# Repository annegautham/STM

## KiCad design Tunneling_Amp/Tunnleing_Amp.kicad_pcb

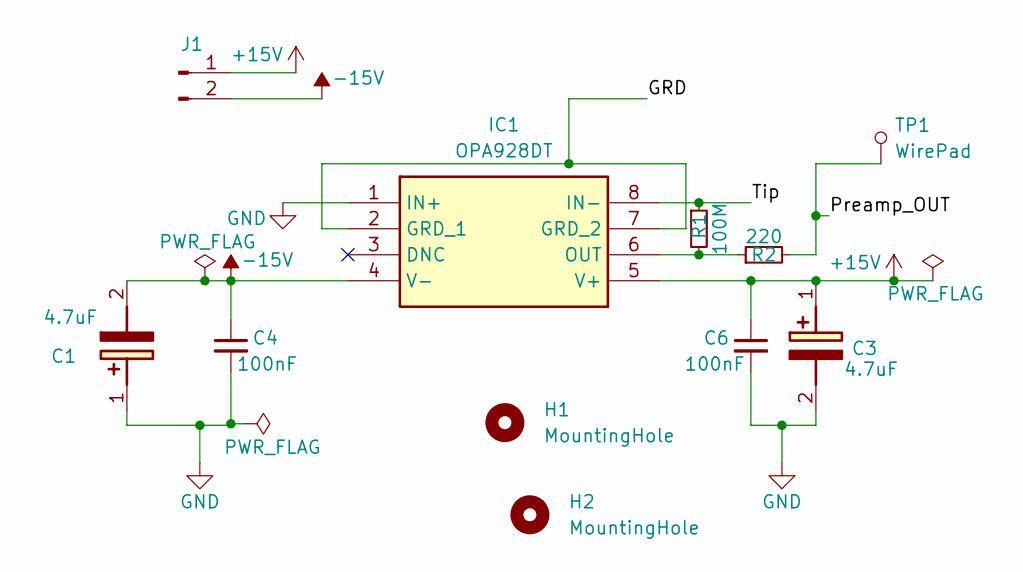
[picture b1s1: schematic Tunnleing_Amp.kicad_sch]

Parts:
C1, C3: 4.7uF; CAPPM6032X280N; Mouser Part Number 74-293D475X9035C2TE3
C4, C6: 100nF; C_0402_1005Metric; LCSC C1545
H1, H2: MountingHole; MountingHole_2.2mm_M2
IC1: OPA928DT; SOIC127P600X175-8N; Mouser Part Number 595-OPA928DT
J1: Conn_01x02_Pin; PinHeader_1x02_P2.54mm_Vertical
R1: 100M; R_0603_1608Metric; Mouser Part Number 708-HMC0603FT100M; LCSC C22962
R2: 220; R_0603_1608Metric; LCSC C22962
TP1: WirePad; PinHeader_1x01_P1.00mm_Vertical

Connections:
+15V: C3.1 (+), C6.1, IC1.5 (V+), J1.1
-15V: C1.2 (-), C4.1, IC1.4 (V-), J1.2
/GRD: IC1.2 (GRD_1), IC1.7 (GRD_2)
/Preamp_OUT: R2.2, TP1.1
/Tip: IC1.8 (IN-), R1.1
GND: C1.1 (+), C3.2 (-), C4.2, C6.2, IC1.1 (IN+)
unnamed: IC1.6 (OUT), R1.2, R2.1

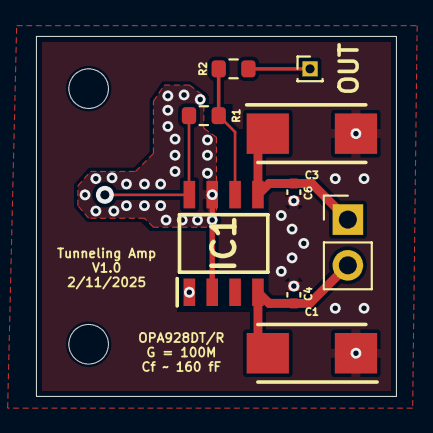
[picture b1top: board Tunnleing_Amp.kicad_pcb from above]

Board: 4 copper layers, 20.0 x 20.0 mm, 11 parts (0 on the bottom side), 7 nets.

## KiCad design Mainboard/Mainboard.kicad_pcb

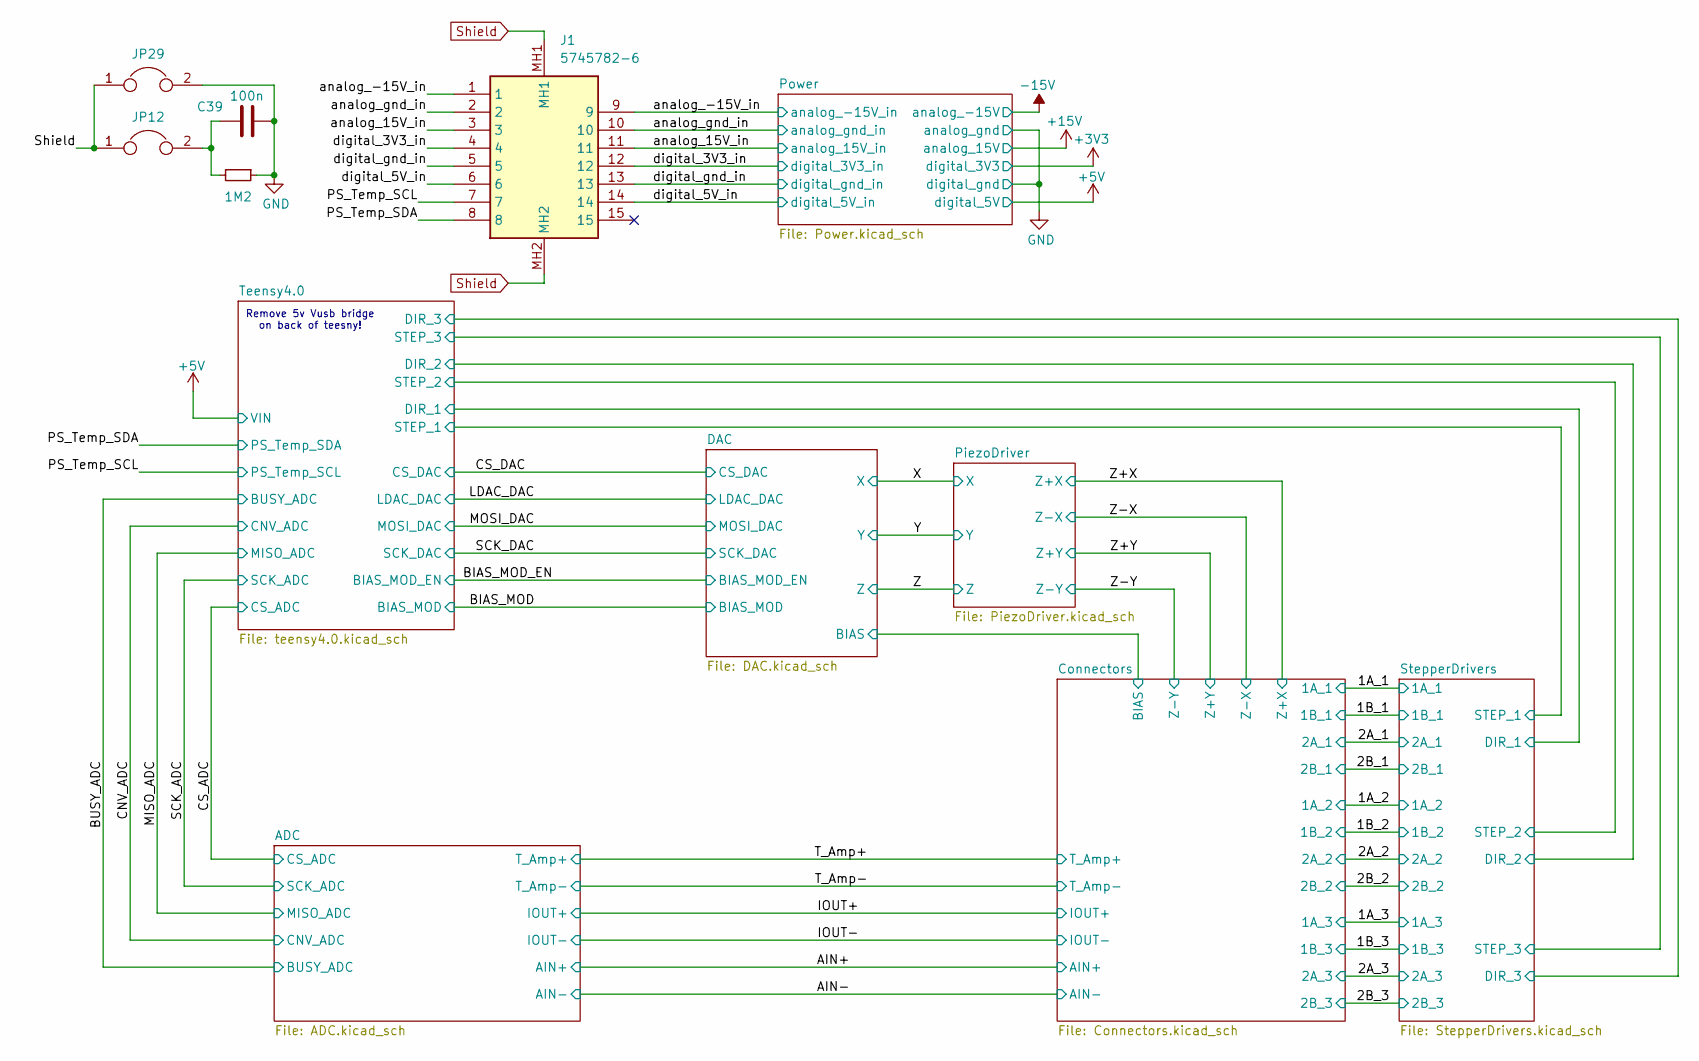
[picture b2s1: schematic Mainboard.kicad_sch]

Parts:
C39: 100n; C_0805_2012Metric; Mouser Part Number 80-C0805S104K1RACAUT; LCSC C14663
J1: 5745782-6; 57457826; Mouser Part Number 571-5745782-6
JP12, JP29: Jumper; SolderJumper-2_P1.3mm_Open_TrianglePad1.0x1.5mm
R30: 1M2; R_0805_2012Metric; Mouser Part Number 755-SDR10EZPF1204; LCSC C22107

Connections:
/PS_Temp_SCL: J1.7; also elsewhere on the board
/PS_Temp_SDA: J1.8; also elsewhere on the board
unnamed: C39.1, JP12.2, R30.2
Shield: J1.MH1, J1.MH2, JP12.1, JP29.1; also elsewhere on the board

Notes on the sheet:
Remove 5v Vusb bridge on back of teesny!

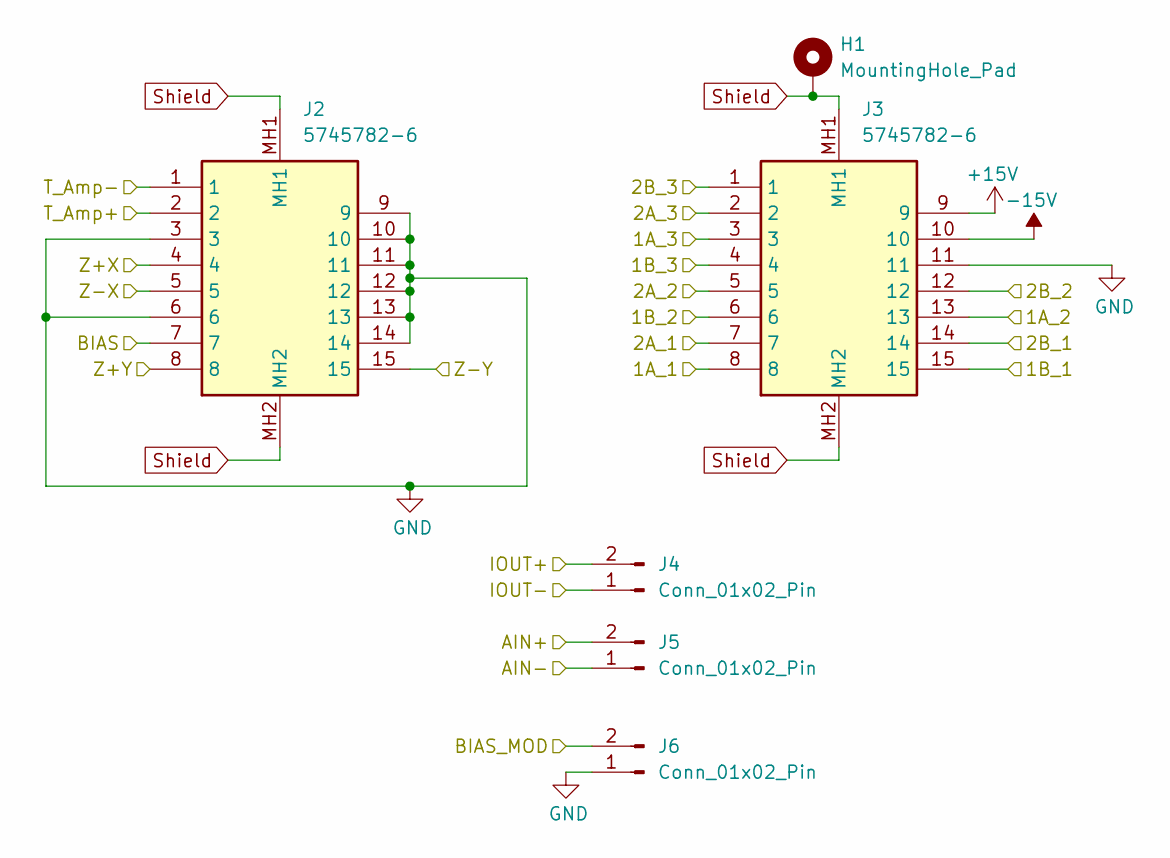
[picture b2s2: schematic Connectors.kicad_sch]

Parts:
H1: MountingHole_Pad; MountingHole_2.2mm_M2_Pad_Via
J2, J3: 5745782-6; 57457826; Mouser Part Number 571-5745782-6
J4, J5, J6: Conn_01x02_Pin; PinHeader_1x02_P2.54mm_Vertical

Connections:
/1A_1: J3.8; also elsewhere on the board
/1A_2: J3.13; also elsewhere on the board
/1A_3: J3.3; also elsewhere on the board
/1B_1: J3.15; also elsewhere on the board
/1B_2: J3.6; also elsewhere on the board
/1B_3: J3.4; also elsewhere on the board
/2A_1: J3.7; also elsewhere on the board
/2A_2: J3.5; also elsewhere on the board
/2A_3: J3.2; also elsewhere on the board
/2B_1: J3.14; also elsewhere on the board
/2B_2: J3.12; also elsewhere on the board
/2B_3: J3.1; also elsewhere on the board
/AIN+: J5.2; also elsewhere on the board
/AIN-: J5.1; also elsewhere on the board
/BIAS_MOD: J6.2; also elsewhere on the board
/Connectors/BIAS: J2.7; also elsewhere on the board
/IOUT+: J4.2; also elsewhere on the board
/IOUT-: J4.1; also elsewhere on the board
/T_Amp+: J2.2; also elsewhere on the board
/T_Amp-: J2.1; also elsewhere on the board
/Z+X: J2.4; also elsewhere on the board
/Z+Y: J2.8; also elsewhere on the board
/Z-X: J2.5; also elsewhere on the board
/Z-Y: J2.15; also elsewhere on the board
Shield: H1.1, J2.MH1, J2.MH2, J3.MH1, J3.MH2; also elsewhere on the board

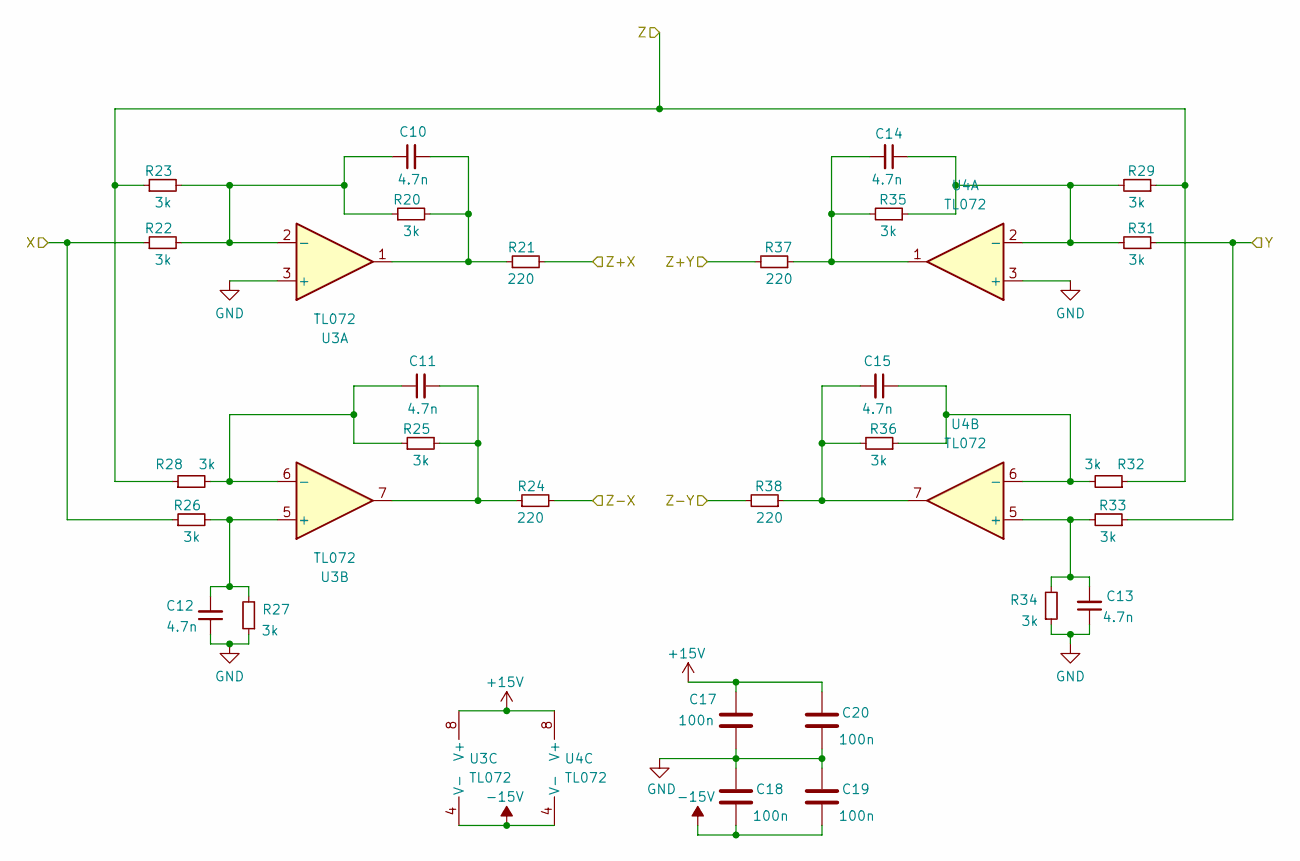
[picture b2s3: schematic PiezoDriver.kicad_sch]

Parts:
C10, C11, C12, C13, C14, C15: 4.7n; C_0805_2012Metric; Mouser Part Number 80-C0805C472J3GAUTO
C17, C18, C19, C20: 100n; C_0805_2012Metric; Mouser Part Number 80-C0805S104K1RACAUT; LCSC C14663
R20, R22, R23, R25, R26, R27, R28, R29, R31, R32, R33, R34, R35, R36: 3k; R_0805_2012Metric; Mouser Part Number 667-ERA-6AED302V
R21, R24, R37, R38: 220; R_0805_2012Metric; Mouser Part Number 279-CRGH0805F220R
U3, U4: TL072; SOIC-8-1EP_3.9x4.9mm_P1.27mm_EP2.29x3mm_ThermalVias; Mouser Part Number 511-TL072BIDT

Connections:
/X: R22.1, R26.1; also elsewhere on the board
/Y: R31.1, R33.1; also elsewhere on the board
/Z: R23.1, R28.1, R29.1, R32.1; also elsewhere on the board
/Z+X: R21.2; also elsewhere on the board
/Z+Y: R37.2; also elsewhere on the board
/Z-X: R24.2; also elsewhere on the board
/Z-Y: R38.2; also elsewhere on the board
unnamed: C10.2, R20.2, R21.1, U3.1
unnamed: C11.2, R24.1, R25.2, U3.7
unnamed: C14.2, R35.2, R37.1, U4.1
unnamed: C15.2, R36.2, R38.1, U4.7
unnamed: C10.1, R20.1, R22.2, R23.2, U3.2 (-)
unnamed: C12.2, R26.2, R27.2, U3.5 (+)
unnamed: C11.1, R25.1, R28.2, U3.6 (-)
unnamed: C14.1, R29.2, R31.2, R35.1, U4.2 (-)
unnamed: C13.2, R33.2, R34.2, U4.5 (+)
unnamed: C15.1, R32.2, R36.1, U4.6 (-)

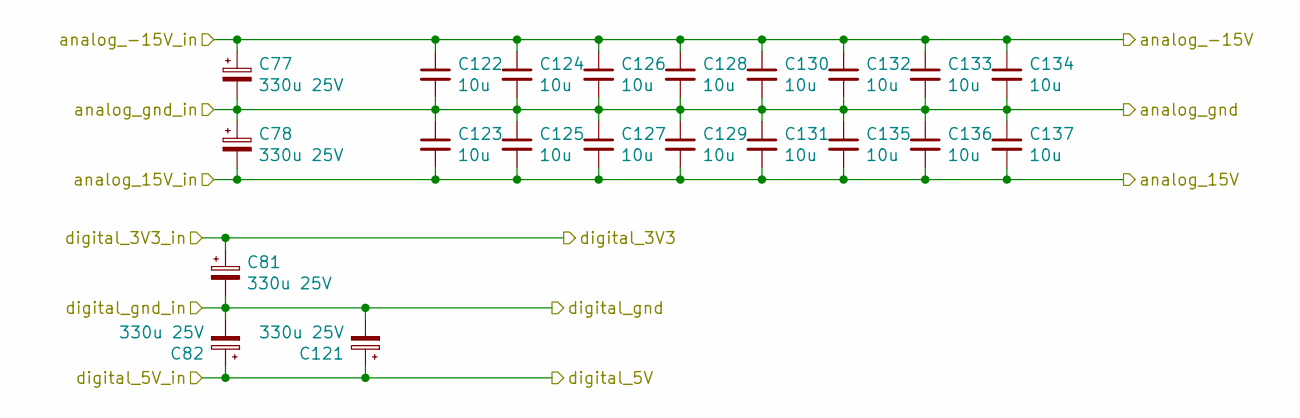
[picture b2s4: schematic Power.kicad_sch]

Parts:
C77, C78, C81, C82, C121: 330u 25V; CP_Radial_D8.0mm_P3.50mm
C122, C123, C124, C125, C126, C127, C128, C129, C130, C131, C132, C133, C134, C135, C136, C137: 10u; C_1206_3216Metric

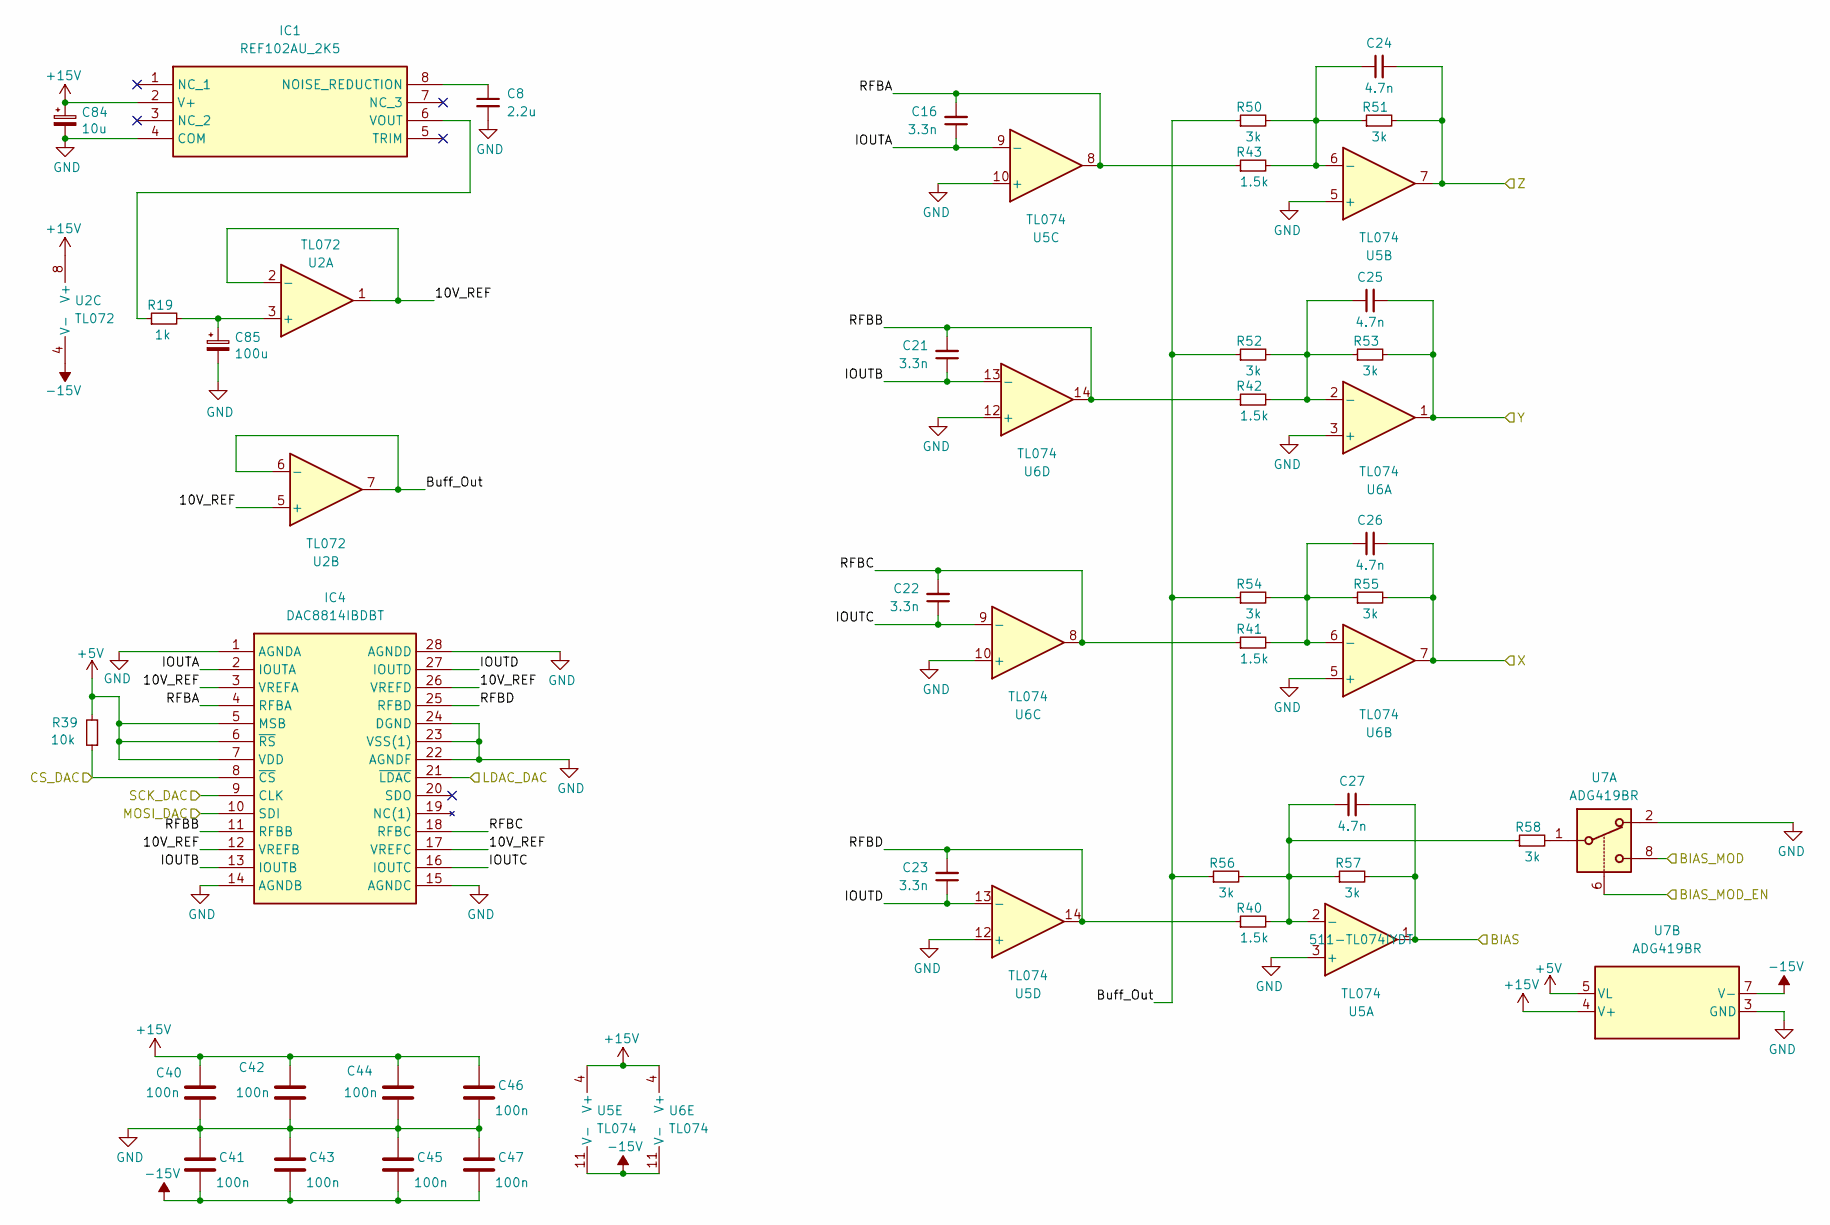
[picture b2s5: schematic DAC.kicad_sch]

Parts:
C8: 2.2u; C_0805_2012Metric; Mouser Part Number 80-C0805C225K4R3123
C16, C21, C22, C23: 3.3n; C_0805_2012Metric; Mouser Part Number 80-C0805C332KCR
C24, C25, C26, C27: 4.7n; C_0805_2012Metric; Mouser Part Number 80-C0805C472J3GAUTO
C40, C41, C42, C43, C44, C45, C46, C47: 100n; C_0805_2012Metric; Mouser Part Number 80-C0805S104K1RACAUT; LCSC C14663
C84: 10u; CP_Radial_D5.0mm_P2.00mm; Mouser Part Number 710-860020472003
C85: 100u; CP_Radial_D6.3mm_P2.50mm; Mouser Part Number 80-ESW107M016AE3EA
IC1: REF102AU_2K5; SOIC127P600X175-8N; Mouser Part Number 595-REF102AU/2K5
IC4: DAC8814IBDBT; SOP65P780X200-28N; Mouser Part Number 595-DAC8814IBDBT
R19: 1k; R_0805_2012Metric; Mouser Part Number 755-ESR10EZPJ102
R39: 10k; R_0805_2012Metric; Mouser Part Number 755-ESR10EZPD1002
R40, R41, R42, R43: 1.5k; R_0805_2012Metric; Mouser Part Number 755-ESR10EZPF1501
R50, R51, R52, R53, R54, R55, R56, R57, R58: 3k; R_0805_2012Metric; Mouser Part Number 667-ERA-6AED302V
U2: TL072; SOIC-8-1EP_3.9x4.9mm_P1.27mm_EP2.29x3mm_ThermalVias; Mouser Part Number 511-TL072BIDT
U5, U6: TL074; SOIC-14_3.9x8.7mm_P1.27mm; Mouser Part Number 511-TL074IYDT
U7: ADG419BR; SOIC-8_3.9x4.9mm_P1.27mm; Mouser Part Number 584-ADG419BRZ-R

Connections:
/BIAS_MOD: U7.8; also elsewhere on the board
/BIAS_MOD_EN: U7.6; also elsewhere on the board
/CS_DAC: IC4.8 (~CS), R39.1; also elsewhere on the board
/Connectors/BIAS: C27.2, R57.2, U5.1; also elsewhere on the board
/DAC/10V_REF: IC4.3 (VREFA), IC4.12 (VREFB), IC4.17 (VREFC), IC4.26 (VREFD), U2.1, U2.2 (-), U2.5 (+)
/DAC/Buff_Out: R50.1, R52.1, R54.1, R56.1, U2.6 (-), U2.7
/DAC/IOUTA: C16.1, IC4.2 (IOUTA), U5.9 (-)
/DAC/IOUTB: C21.1, IC4.13 (IOUTB), U6.13 (-)
/DAC/IOUTC: C22.1, IC4.16 (IOUTC), U6.9 (-)
/DAC/IOUTD: C23.1, IC4.27 (IOUTD), U5.13 (-)
/DAC/RFBA: C16.2, IC4.4 (RFBA), R43.1, U5.8
/DAC/RFBB: C21.2, IC4.11 (RFBB), R42.1, U6.14
/DAC/RFBC: C22.2, IC4.18 (RFBC), R41.1, U6.8
/DAC/RFBD: C23.2, IC4.25 (RFBD), R40.1, U5.14
/LDAC_DAC: IC4.21 (~LDAC); also elsewhere on the board
/MOSI_DAC: IC4.10 (SDI); also elsewhere on the board
/SCK_ADC: IC4.9 (CLK); also elsewhere on the board
/X: C26.2, R55.2, U6.7; also elsewhere on the board
/Y: C25.2, R53.2, U6.1; also elsewhere on the board
/Z: C24.2, R51.2, U5.7; also elsewhere on the board
unnamed: C8.1, IC1.8 (NOISE_REDUCTION)
unnamed: IC1.6 (VOUT), R19.1
unnamed: R58.2, U7.1
unnamed: C85.1, R19.2, U2.3 (+)
unnamed: C27.1, R40.2, R56.2, R57.1, R58.1, U5.2 (-)
unnamed: C24.1, R43.2, R50.2, R51.1, U5.6 (-)
unnamed: C25.1, R42.2, R52.2, R53.1, U6.2 (-)
unnamed: C26.1, R41.2, R54.2, R55.1, U6.6 (-)

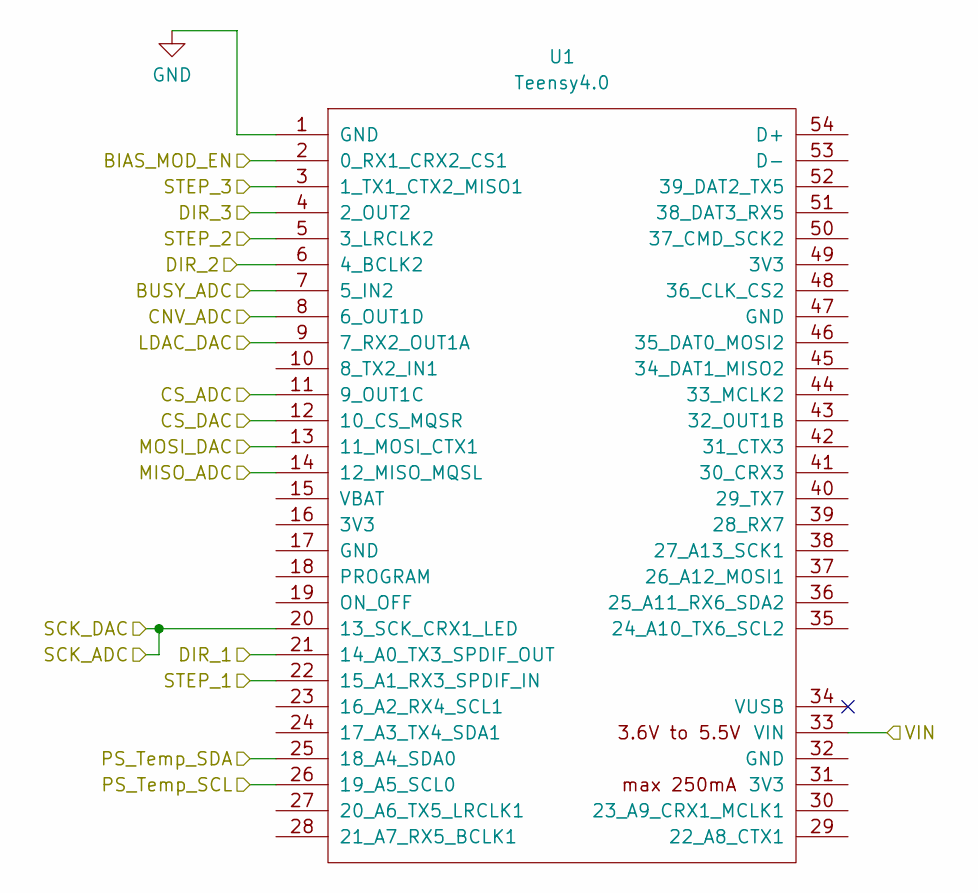
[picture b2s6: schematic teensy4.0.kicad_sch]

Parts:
U1: Teensy4.0; Teensy40

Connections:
/BIAS_MOD_EN: U1.2 (0_RX1_CRX2_CS1); also elsewhere on the board
/BUSY_ADC: U1.7 (5_IN2); also elsewhere on the board
/CNV_ADC: U1.8 (6_OUT1D); also elsewhere on the board
/CS_ADC: U1.11 (9_OUT1C); also elsewhere on the board
/CS_DAC: U1.12 (10_CS_MQSR); also elsewhere on the board
/LDAC_DAC: U1.9 (7_RX2_OUT1A); also elsewhere on the board
/MISO_ADC: U1.14 (12_MISO_MQSL); also elsewhere on the board
/MOSI_DAC: U1.13 (11_MOSI_CTX1); also elsewhere on the board
/PS_Temp_SCL: U1.26 (19_A5_SCL0); also elsewhere on the board
/PS_Temp_SDA: U1.25 (18_A4_SDA0); also elsewhere on the board
/SCK_ADC: U1.20 (13_SCK_CRX1_LED); also elsewhere on the board
/StepperDrivers/DIR_1: U1.21 (14_A0_TX3_SPDIF_OUT); also elsewhere on the board
/StepperDrivers/DIR_2: U1.6 (4_BCLK2); also elsewhere on the board
/StepperDrivers/DIR_3: U1.4 (2_OUT2); also elsewhere on the board
/StepperDrivers/STEP_1: U1.22 (15_A1_RX3_SPDIF_IN); also elsewhere on the board
/StepperDrivers/STEP_2: U1.5 (3_LRCLK2); also elsewhere on the board
/StepperDrivers/STEP_3: U1.3 (1_TX1_CTX2_MISO1); also elsewhere on the board

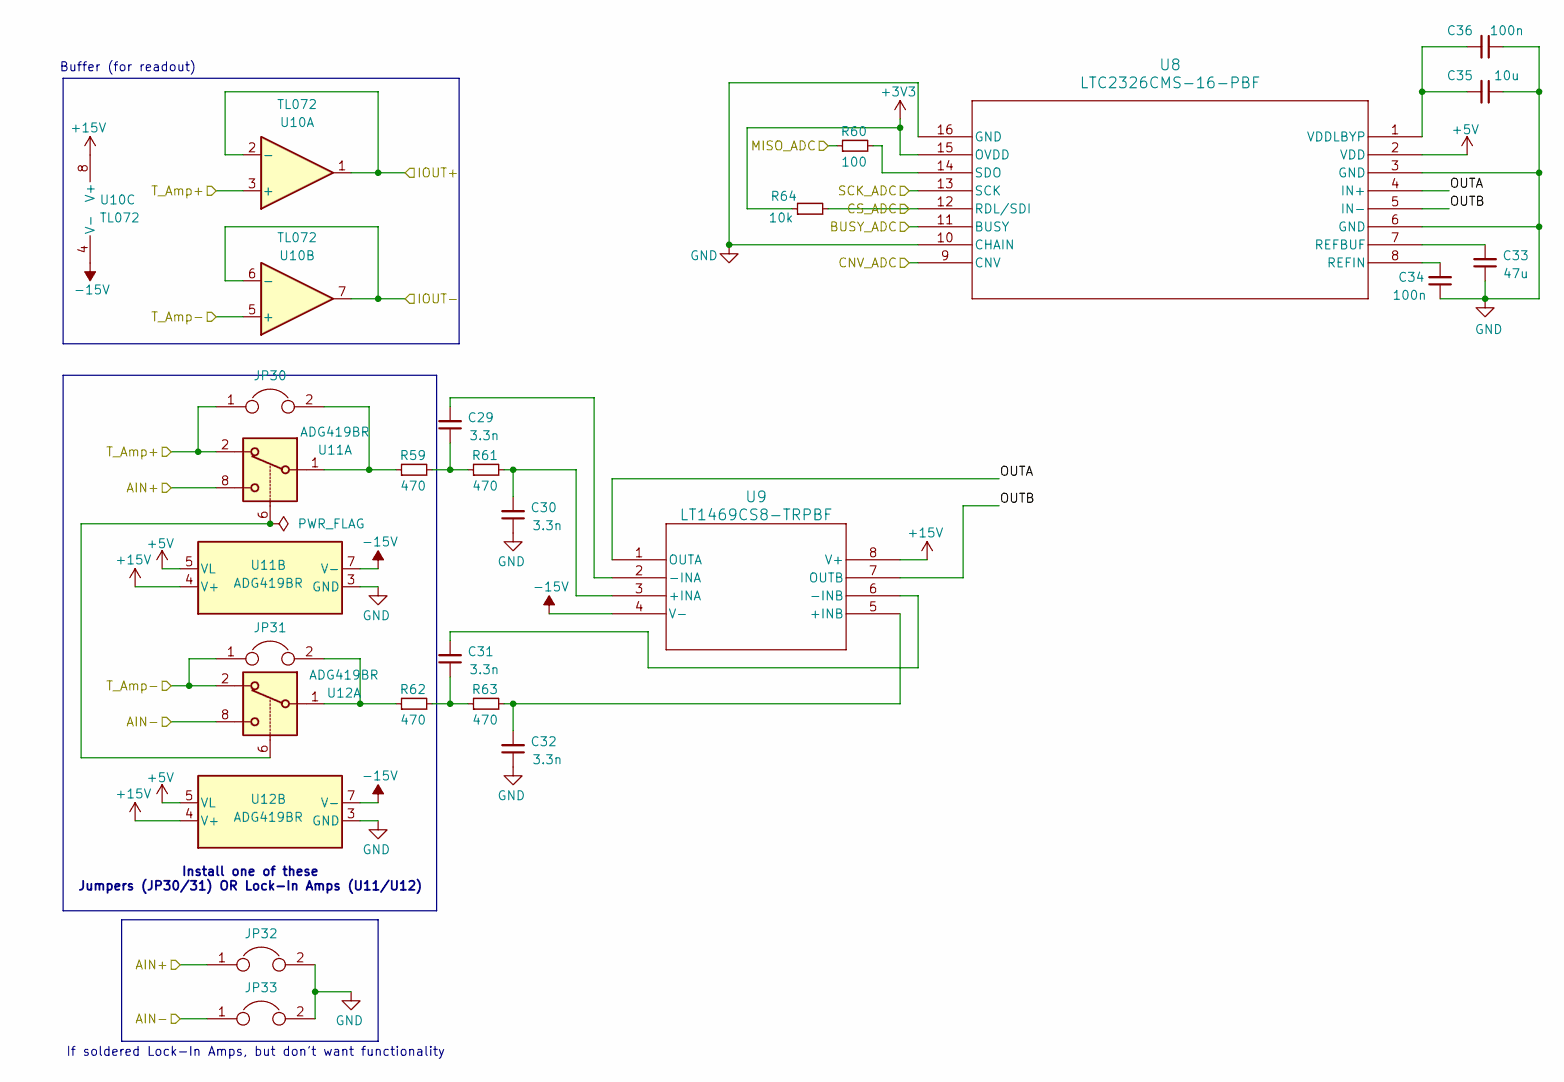
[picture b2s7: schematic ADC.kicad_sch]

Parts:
C29, C30, C31, C32: 3.3n; C_0805_2012Metric; Mouser Part Number 80-C0805C332KCR
C33: 47u; C_0805_2012Metric; Mouser Part Number 80-C0805C476M9P7800
C34, C36: 100n; C_0805_2012Metric; Mouser Part Number 80-C0805S104K1RACAUT
C35: 10u; CP_Radial_D5.0mm_P2.00mm; Mouser Part Number 710-860020472003
JP30, JP31, JP32, JP33: Jumper; SolderJumper-2_P1.3mm_Open_TrianglePad1.0x1.5mm
R59, R61, R62, R63: 470; R_0805_2012Metric; Mouser Part Number 667-ERA-6AEB471V
R60: 100; R_0805_2012Metric; Mouser Part Number 708-RNCA0805BTE100R
R64: 10k; R_0805_2012Metric; Mouser Part Number 755-ESR10EZPD1002
U8: LTC2326CMS-16-PBF; MSOP-16_MS_LIT; Mouser Part Number 584-LTC2326CMS-16PBF
U9: LT1469CS8-TRPBF; SO-8_S_LIT; Mouser Part Number 584-LT1469CS8#TRPBF
U10: TL072; SOIC-8-1EP_3.9x4.9mm_P1.27mm_EP2.29x3mm_ThermalVias; Mouser Part Number 511-TL072BIDT
U11, U12: ADG419BR; SOIC-8_3.9x4.9mm_P1.27mm; Mouser Part Number 584-ADG419BRZ-R

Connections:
/ADC/OUTA: U8.4 (IN+), U9.1 (OUTA)
/ADC/OUTB: U8.5 (IN-), U9.7 (OUTB)
/AIN+: JP32.1, U11.8; also elsewhere on the board
/AIN-: JP33.1, U12.8; also elsewhere on the board
/BUSY_ADC: U8.11 (BUSY); also elsewhere on the board
/CNV_ADC: U8.9 (CNV); also elsewhere on the board
/CS_ADC: R64.2, U8.12 (RDL/SDI); also elsewhere on the board
/IOUT+: U10.1, U10.2 (-); also elsewhere on the board
/IOUT-: U10.6 (-), U10.7; also elsewhere on the board
/MISO_ADC: R60.1; also elsewhere on the board
/SCK_ADC: U8.13 (SCK); also elsewhere on the board
/T_Amp+: JP30.1, U10.3 (+), U11.2; also elsewhere on the board
/T_Amp-: JP31.1, U10.5 (+), U12.2; also elsewhere on the board
unnamed: C29.1, R59.2, R61.1
unnamed: C31.1, R62.2, R63.1
unnamed: JP30.2, R59.1, U11.1
unnamed: JP31.2, R62.1, U12.1
unnamed: C33.2, U8.7 (REFBUF)
unnamed: C34.2, U8.8 (REFIN)
unnamed: R60.2, U8.14 (SDO)
unnamed: C35.2, C36.2, U8.1 (VDDLBYP)
unnamed: C30.2, R61.2, U9.3 (+INA)
unnamed: C32.2, R63.2, U9.5 (+INB)
unnamed: C29.2, U9.2 (-INA)
unnamed: C31.2, U9.6 (-INB)
unnamed: U11.6, U12.6

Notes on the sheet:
Install one of these Jumpers (JP30/31) OR Lock-In Amps (U11/U12)
If soldered Lock-In Amps, but don't want functionality
Buffer (for readout)

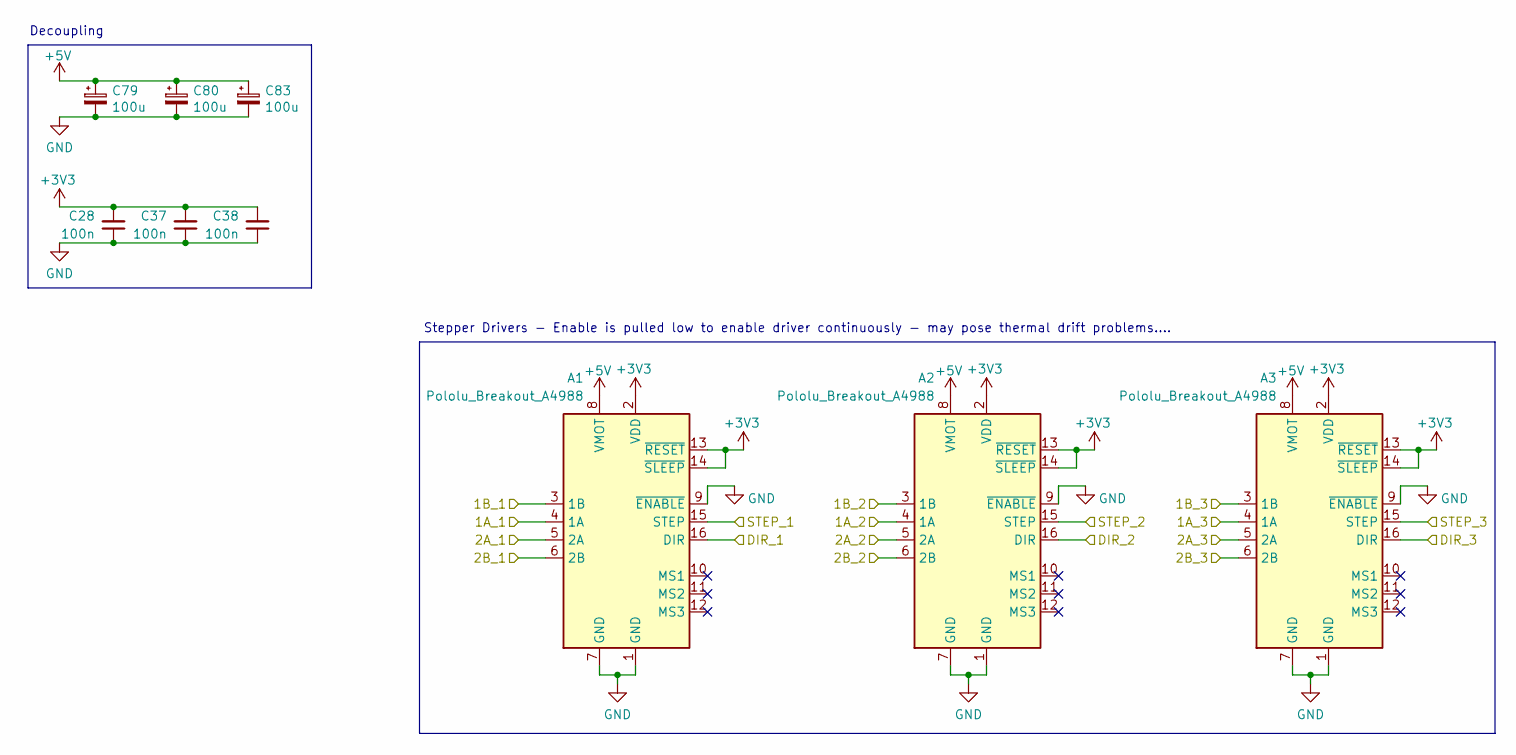
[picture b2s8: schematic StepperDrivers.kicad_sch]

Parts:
A1, A2, A3: Pololu_Breakout_A4988; Pololu_Breakout-16_15.2x20.3mm
C28, C37, C38: 100n; C_0805_2012Metric; Mouser Part Number 80-C0805S104K1RACAUT
C79, C80, C83: 100u; CP_Radial_D6.3mm_P2.50mm; Mouser Part Number 80-ESW107M016AE3EA

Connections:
/1A_1: A1.4 (1A); also elsewhere on the board
/1A_2: A2.4 (1A); also elsewhere on the board
/1A_3: A3.4 (1A); also elsewhere on the board
/1B_1: A1.3 (1B); also elsewhere on the board
/1B_2: A2.3 (1B); also elsewhere on the board
/1B_3: A3.3 (1B); also elsewhere on the board
/2A_1: A1.5 (2A); also elsewhere on the board
/2A_2: A2.5 (2A); also elsewhere on the board
/2A_3: A3.5 (2A); also elsewhere on the board
/2B_1: A1.6 (2B); also elsewhere on the board
/2B_2: A2.6 (2B); also elsewhere on the board
/2B_3: A3.6 (2B); also elsewhere on the board
/StepperDrivers/DIR_1: A1.16 (DIR); also elsewhere on the board
/StepperDrivers/DIR_2: A2.16 (DIR); also elsewhere on the board
/StepperDrivers/DIR_3: A3.16 (DIR); also elsewhere on the board
/StepperDrivers/STEP_1: A1.15 (STEP); also elsewhere on the board
/StepperDrivers/STEP_2: A2.15 (STEP); also elsewhere on the board
/StepperDrivers/STEP_3: A3.15 (STEP); also elsewhere on the board

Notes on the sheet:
Stepper Drivers - Enable is pulled low to enable driver continuously - may pose thermal drift problems....
Decoupling

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
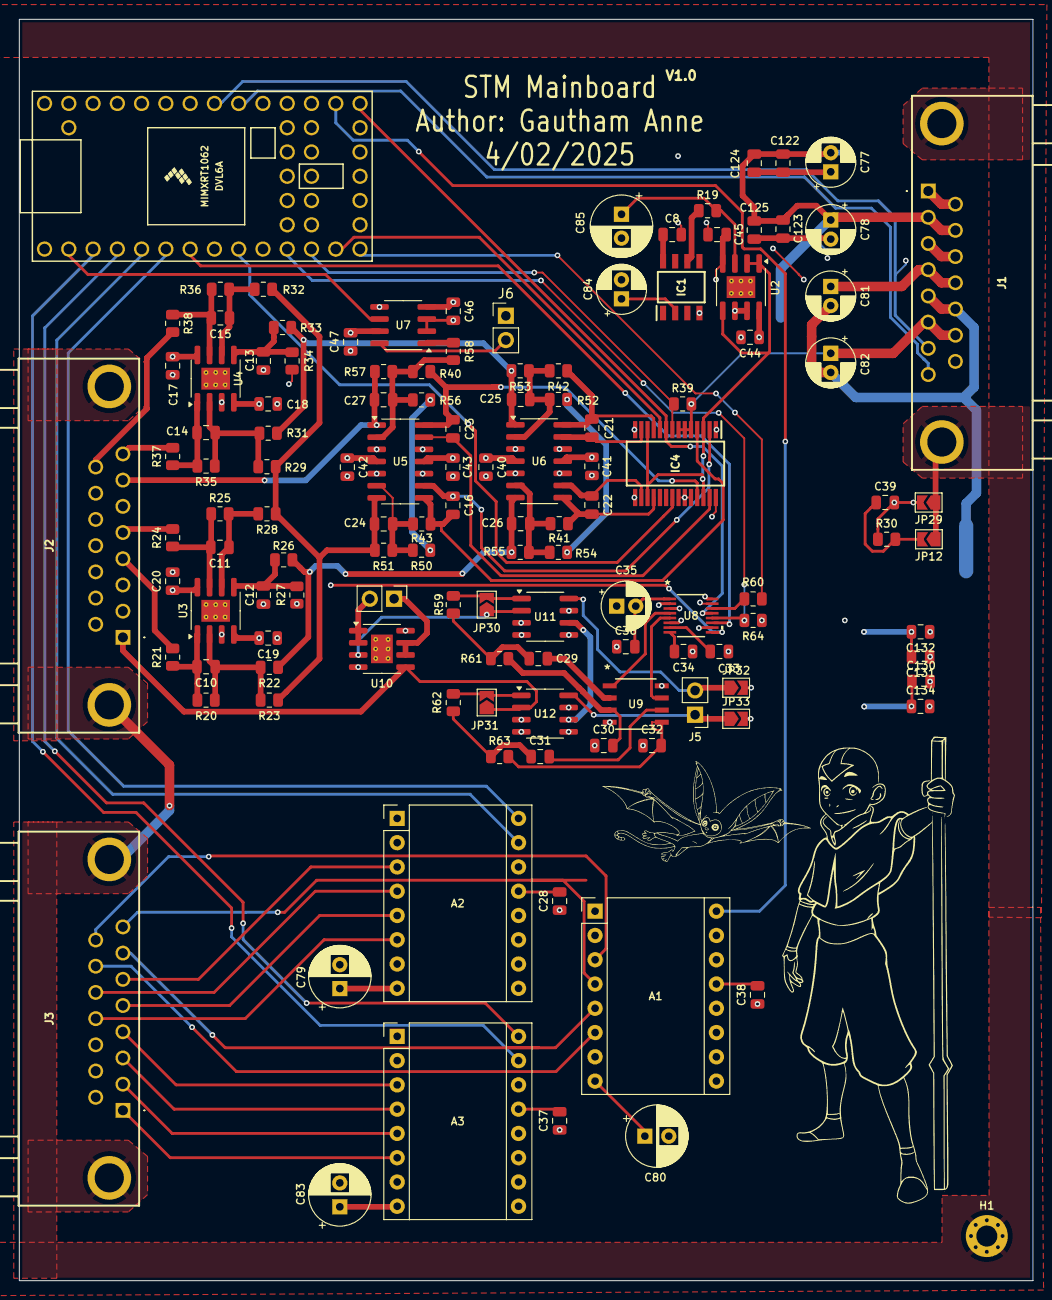
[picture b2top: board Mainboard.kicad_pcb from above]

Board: 4 copper layers, 106.1 x 132.0 mm, 126 parts (0 on the bottom side), 94 nets.

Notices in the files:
Firmware/Berard/Teensy/STM_Controller/STM_Controller.ino:
Copyright (c) Daniel Berard, daniel.berard@mail.mcgill.ca
